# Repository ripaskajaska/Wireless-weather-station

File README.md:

# Wireless-weather-station
Aalto University’s ELEC-8701 Elektronics workshop courses repository for Axel Soderberg, Roope Jaskari and Kalle Aro

# Basic git usage for this project:

Sections 1 to 2 are done on the command line
# 1. Initialization 

If you don't have an ssh key yet follow the instruction in [this link](https://www.howtogeek.com/762863/how-to-generate-ssh-keys-in-windows-10-and-windows-11/)
Add this ssh key to your GitHub SSH keys and proceed.

## clone project
```
git clone git@github.com:<yourusername>/Wireless-weather-station.git
```

Go to the cloned repository > "Wireless-weather-station" (default name)

## Make your own branch
```
git branch <your own branch name here>
```
```
git checkout <your own branch name here>
```
# 2. Working with git

When you want to commit something, first check out the changes you have made.
```
git status
```
After this add the files you'd like to commit

```
git add <your file/folder in the git initialized folder>
```
Commit
```
git commit -m "<your required message here>"
```
And if this is your first push to the git repository use this to also set your upstream:

```
git push --set-upstream origin
```
Otherwise:
```
git push
```

# 3. Merging with main
After a successful commit and push, if you'd like to begin a merge request with your branch and the main branch, navigate to your branch in GitHub from this dropdown:

And then make a pull request here: 

After this, notify the other contributors about the pull request in order to get their approval on the matter. Success!

# In addition one can delete their own branch from the GitHub to start a new addition to the project from a clean table. 
# DO NOT TRY TO DELETE THE MAIN BRANCH!

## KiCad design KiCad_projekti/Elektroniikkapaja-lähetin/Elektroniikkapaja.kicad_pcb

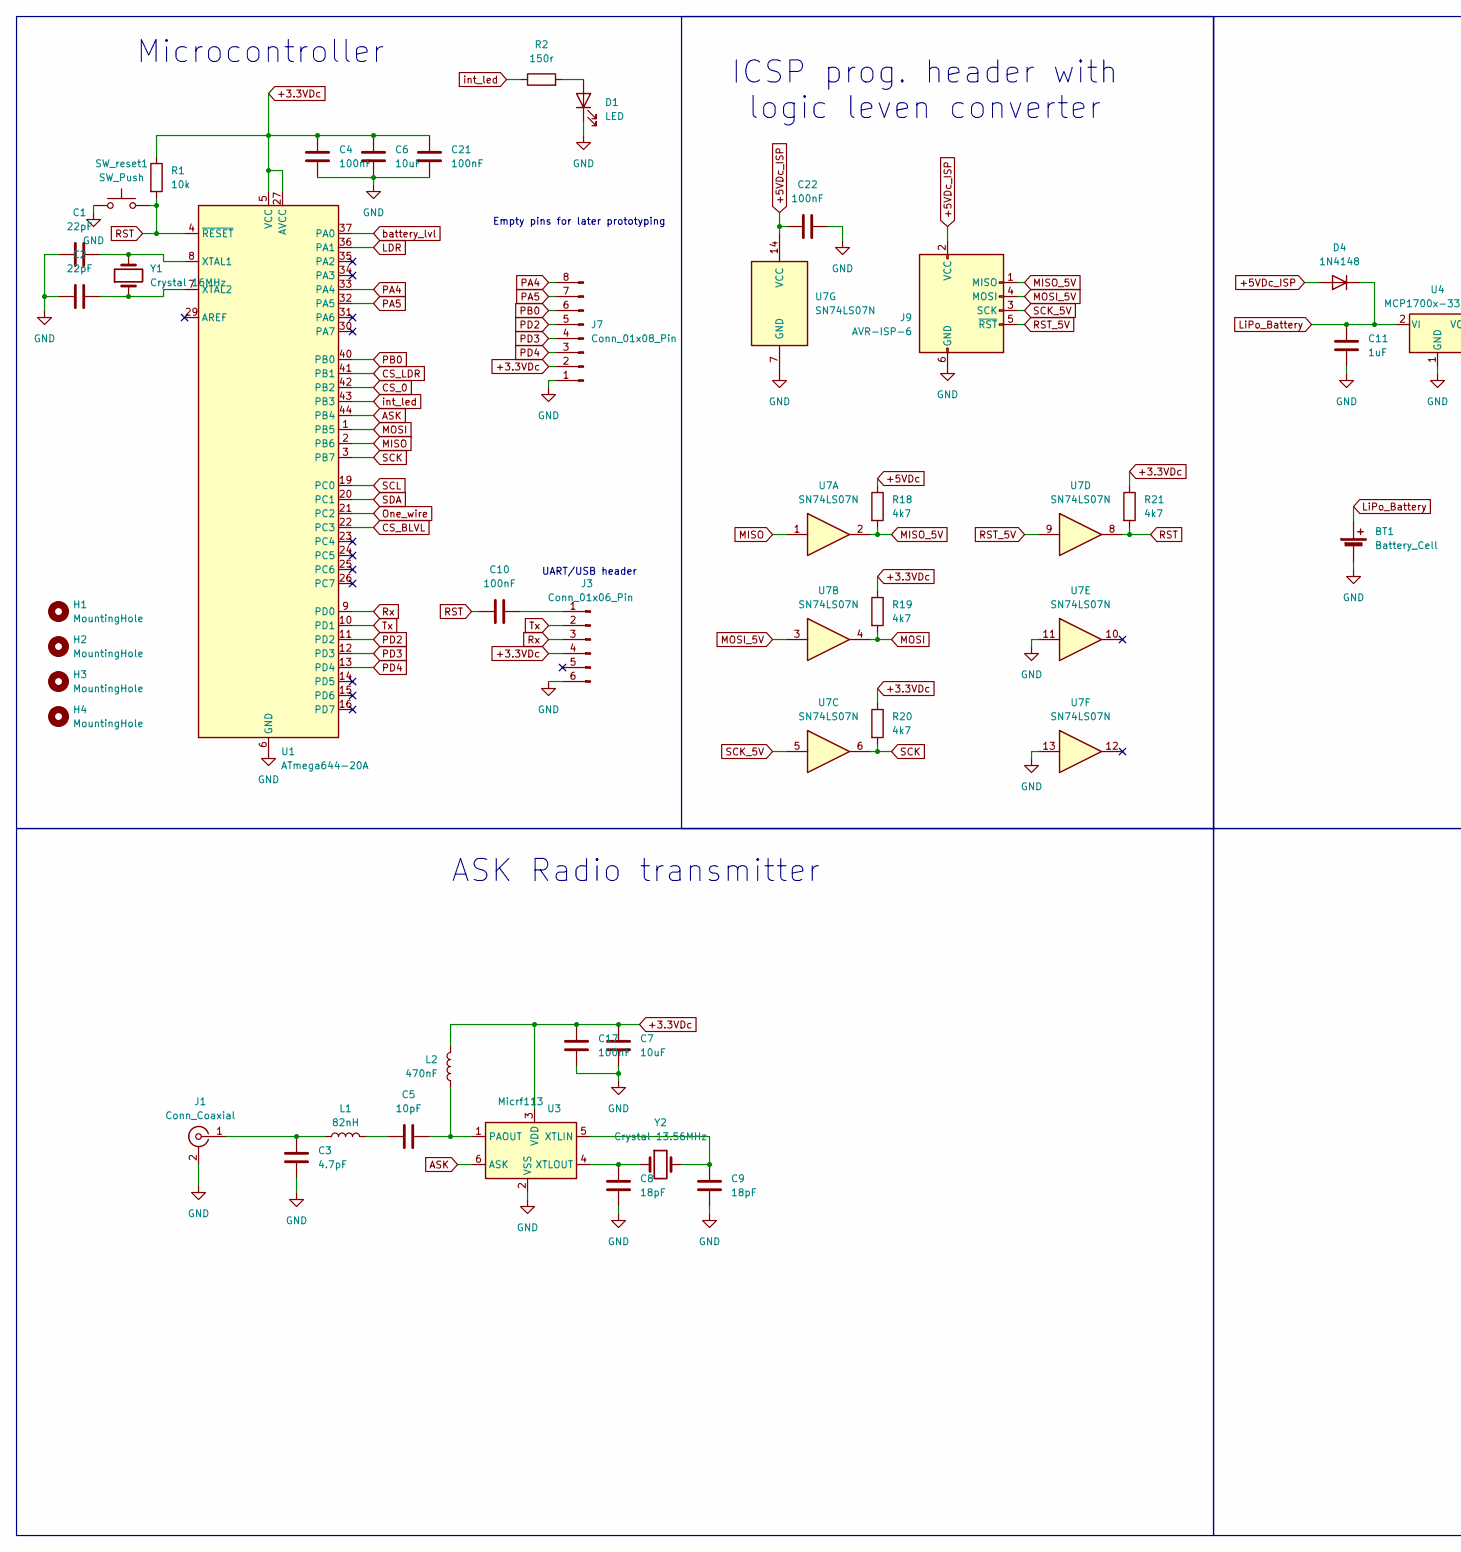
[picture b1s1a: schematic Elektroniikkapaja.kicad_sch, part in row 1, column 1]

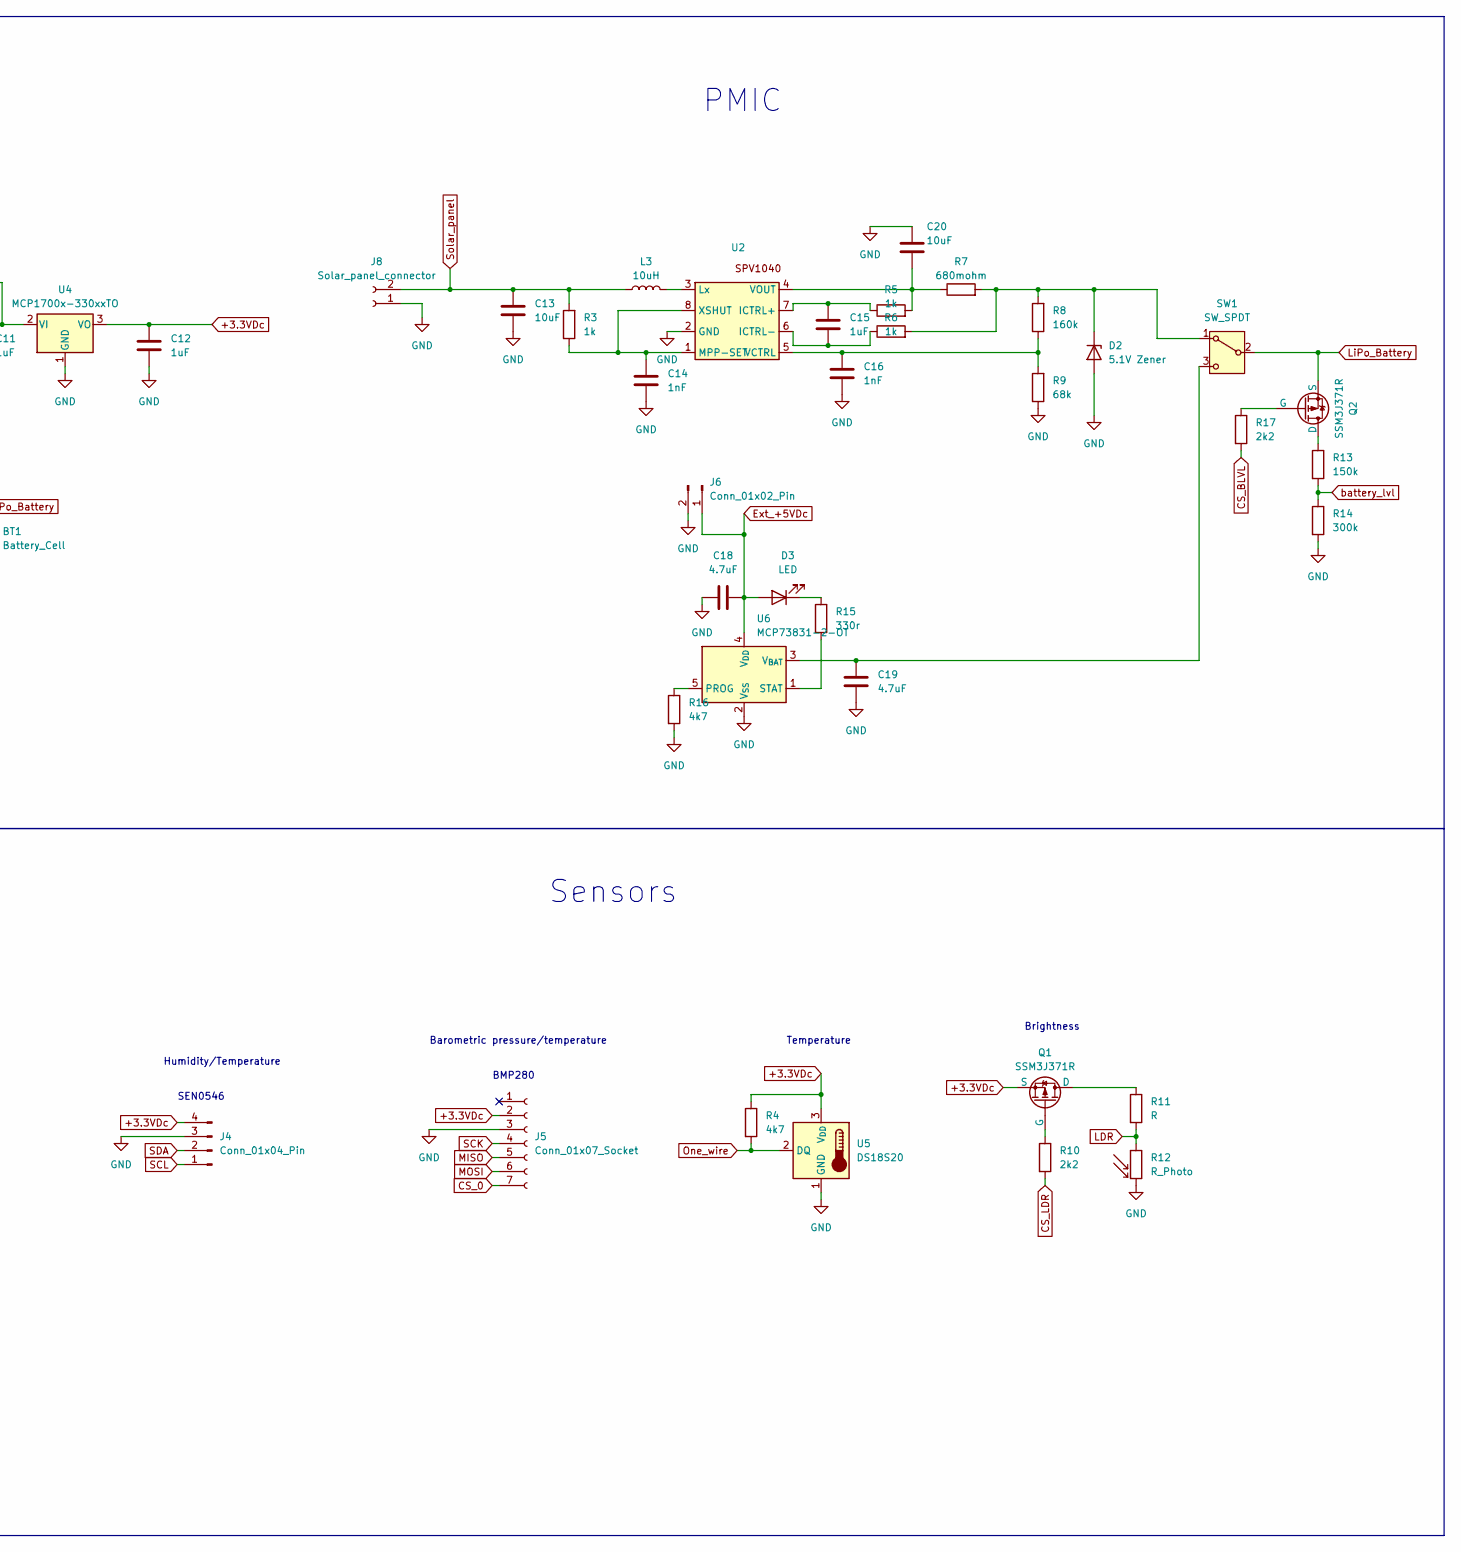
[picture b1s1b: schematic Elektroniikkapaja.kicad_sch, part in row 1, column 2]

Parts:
BT1: Battery_Cell; BatteryHolder_MPD_BH-18650-PC2
C1, C2: 22pF; C_0805_2012Metric_Pad1.18x1.45mm_HandSolder
C3: 4.7pF; C_0805_2012Metric_Pad1.18x1.45mm_HandSolder
C4, C10, C17, C21, C22: 100nF; C_0805_2012Metric_Pad1.18x1.45mm_HandSolder
C5: 10pF; C_0805_2012Metric_Pad1.18x1.45mm_HandSolder
C6, C7, C13, C20: 10uF; C_0805_2012Metric_Pad1.18x1.45mm_HandSolder
C8, C9: 18pF; C_0805_2012Metric_Pad1.18x1.45mm_HandSolder
C11, C12, C15: 1uF; C_0805_2012Metric_Pad1.18x1.45mm_HandSolder
C14, C16: 1nF; C_0805_2012Metric_Pad1.18x1.45mm_HandSolder
C18, C19: 4.7uF; C_1206_3216Metric_Pad1.33x1.80mm_HandSolder
D1, D3: LED; LED_0805_2012Metric_Pad1.15x1.40mm_HandSolder
D2: 5.1V Zener; D_DO-35_SOD27_P7.62mm_Horizontal
D4: 1N4148; D_DO-35_SOD27_P7.62mm_Horizontal
H1, H2, H3, H4: MountingHole; MountingHole_2.2mm_M2
J1: Conn_Coaxial; SMA_Amphenol_901-143_Horizontal
J3: Conn_01x06_Pin; PinHeader_1x06_P2.54mm_Vertical
J4: Conn_01x04_Pin; PinHeader_1x04_P2.54mm_Vertical
J5: Conn_01x07_Socket; PinSocket_1x07_P2.54mm_Vertical
J6: Conn_01x02_Pin; PinHeader_1x02_P2.54mm_Vertical
J7: Conn_01x08_Pin; PinHeader_1x08_P2.54mm_Vertical
J8: Solar_panel_connector; PinHeader_1x02_P2.54mm_Vertical
J9: AVR-ISP-6; PinHeader_2x03_P2.54mm_Vertical
L1: 82nH; L_0805_2012Metric_Pad1.15x1.40mm_HandSolder
L2: 470nF; L_0805_2012Metric_Pad1.15x1.40mm_HandSolder
L3: 10uH; WE-PD2_1054
Q1, Q2: SSM3J371R; SOT-23-3
R1: 10k; R_0805_2012Metric_Pad1.20x1.40mm_HandSolder
R2: 150r; R_0805_2012Metric_Pad1.20x1.40mm_HandSolder
R3, R5, R6: 1k; R_0805_2012Metric_Pad1.20x1.40mm_HandSolder
R4, R16, R18, R19, R20, R21: 4k7; R_0805_2012Metric_Pad1.20x1.40mm_HandSolder
R7: 680mohm; R_0805_2012Metric_Pad1.20x1.40mm_HandSolder
R8: 160k; R_0805_2012Metric_Pad1.20x1.40mm_HandSolder
R9: 68k; R_0805_2012Metric_Pad1.20x1.40mm_HandSolder
R10, R17: 2k2; R_0805_2012Metric_Pad1.20x1.40mm_HandSolder
R11: R; R_0805_2012Metric_Pad1.20x1.40mm_HandSolder
R12: R_Photo; R_Axial_DIN0204_L3.6mm_D1.6mm_P2.54mm_Vertical
R13: 150k; R_0805_2012Metric_Pad1.20x1.40mm_HandSolder
R14: 300k; R_0805_2012Metric_Pad1.20x1.40mm_HandSolder
R15: 330r; R_0805_2012Metric_Pad1.20x1.40mm_HandSolder
SW1: SW_SPDT; SW_CuK_JS202011CQN_DPDT_Straight
SW_reset1: SW_Push; SW_SPST_TL3305A
U1: ATmega644-20A; TQFP-44_10x10mm_P0.8mm
U2: TSSOP-8_4.4x3mm_P0.65mm
U3: Micrf113; SOT-23-6_Handsoldering
U4: MCP1700x-330xxTO; TO-92_Inline
U5: DS18S20; TO-92_Inline
U6: MCP73831-2-OT; SOT-23-5
U7: SN74LS07N; DIP-14_W7.62mm
Y1: Crystal 16MHz; Crystal_HC49-U_Vertical
Y2: Crystal 13.56MHz; Crystal_HC49-U_Vertical

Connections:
+3.3VDc: C4.1, C6.1, C7.1, C12.1, C17.2, C21.1, J3.4, J4.4, J5.2, J7.2, L2.1, Q1.2 (S), R1.1, R4.1, R19.1, R20.1, R21.1, U1.5 (VCC), U1.17 (VCC), U1.27 (AVCC), U1.38 (VCC), U3.3 (VDD), U4.3 (VO), U5.3 (V_{DD})
+5VDc: R18.1
+5VDc_ISP: C22.1, D4.2 (A), J9.2 (VCC), U7.14 (VCC)
ASK: U1.44 (PB4), U3.6 (ASK)
CS_0: J5.7, U1.42 (PB2)
CS_BLVL: R17.2, U1.22 (PC3)
CS_LDR: R10.2, U1.41 (PB1)
Ext_+5VDc: C18.1, D3.2 (A), J6.1, U6.4 (V_{DD})
GND: BT1.2 (-), C1.1, C2.1, C3.2, C4.2, C6.2, C7.2, C8.2, C9.2, C11.2, C12.2, C13.2, C14.2, C16.2, C17.1, C18.2, C19.2, C20.1, C21.2, C22.2, D1.1 (K), D2.2 (A), J1.2 (Ext), J3.6, J4.3, J5.3, J6.2, J7.1, J8.1, J9.6 (GND), R9.1, R12.2, R14.2, R16.2, SW_reset1.1, U1.6 (GND), U1.18 (GND), U1.28 (GND), U1.39 (GND), U2.2 (GND), U3.2 (VSS), U4.1 (GND), U5.1 (GND), U6.2 (V_{SS}), U7.7 (GND), U7.11, U7.13
LDR: R11.2, R12.1, U1.36 (PA1)
LiPo_Battery: BT1.1 (+), C11.1, D4.1 (K), Q2.2 (S), SW1.2 (B), U4.2 (VI)
MISO: J5.5, U1.2 (PB6), U7.1
MISO_5V: J9.1 (MISO), R18.2, U7.2
MOSI: J5.6, R19.2, U1.1 (PB5), U7.4
MOSI_5V: J9.4 (MOSI), U7.3
unnamed: C5.1, L1.2
unnamed: D1.2 (A), R2.2
unnamed: D2.1 (K), R6.2, R7.2, R8.2, SW1.1 (A)
unnamed: D3.1 (K), R15.1
unnamed: C3.1, J1.1 (In), L1.1
unnamed: C10.2, J3.1
unnamed: Q1.3 (D), R11.1
unnamed: Q1.1 (G), R10.1
unnamed: Q2.3 (D), R13.1
unnamed: Q2.1 (G), R17.1
unnamed: C19.1, SW1.3 (C), U6.3 (V_{BAT})
unnamed: C1.2, U1.8 (XTAL1), Y1.2
unnamed: C2.2, U1.7 (XTAL2), Y1.1
unnamed: C15.1, R5.1, U2.7 (ICTRL+)
unnamed: C15.2, R6.1, U2.6 (ICTRL-)
unnamed: L3.2, U2.3 (Lx)
unnamed: C14.1, R3.1, U2.1 (MPP-SET), U2.8 (XSHUT)
unnamed: C16.1, R8.1, R9.2, U2.5 (VCTRL)
unnamed: C20.2, R5.2, R7.1, U2.4 (VOUT)
unnamed: C5.2, L2.2, U3.1 (PAOUT)
unnamed: C9.1, U3.5 (XTLIN), Y2.2
unnamed: C8.1, U3.4 (XTLOUT), Y2.1
unnamed: R16.1, U6.5 (PROG)
unnamed: R15.2, U6.1 (STAT)
One_wire: R4.2, U1.21 (PC2), U5.2 (DQ)
PA4: J7.8, U1.33 (PA4)
PA5: J7.7, U1.32 (PA5)
PB0: J7.6, U1.40 (PB0)
PD2: J7.5, U1.11 (PD2)
PD3: J7.4, U1.12 (PD3)
PD4: J7.3, U1.13 (PD4)
RST: C10.1, R1.2, R21.2, SW_reset1.2, U1.4 (~RESET), U7.8
RST_5V: J9.5 (~RST), U7.9
Rx: J3.3, U1.9 (PD0)
SCK: J5.4, R20.2, U1.3 (PB7), U7.6
SCK_5V: J9.3 (SCK), U7.5
SCL: J4.1, U1.19 (PC0)
SDA: J4.2, U1.20 (PC1)
Solar_panel: C13.1, J8.2, L3.1, R3.2
Tx: J3.2, U1.10 (PD1)
battery_lvl: R13.2, R14.1, U1.37 (PA0)
int_led: R2.1, U1.43 (PB3)

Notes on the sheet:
Temperature
Empty pins for later prototyping
UART/USB header
Microcontroller
Humidity/Temperature
PMIC
Barometric pressure/temperature
BMP280
ICSP prog. header with logic leven converter
ASK Radio transmitter
SEN0546
Brightness
Sensors

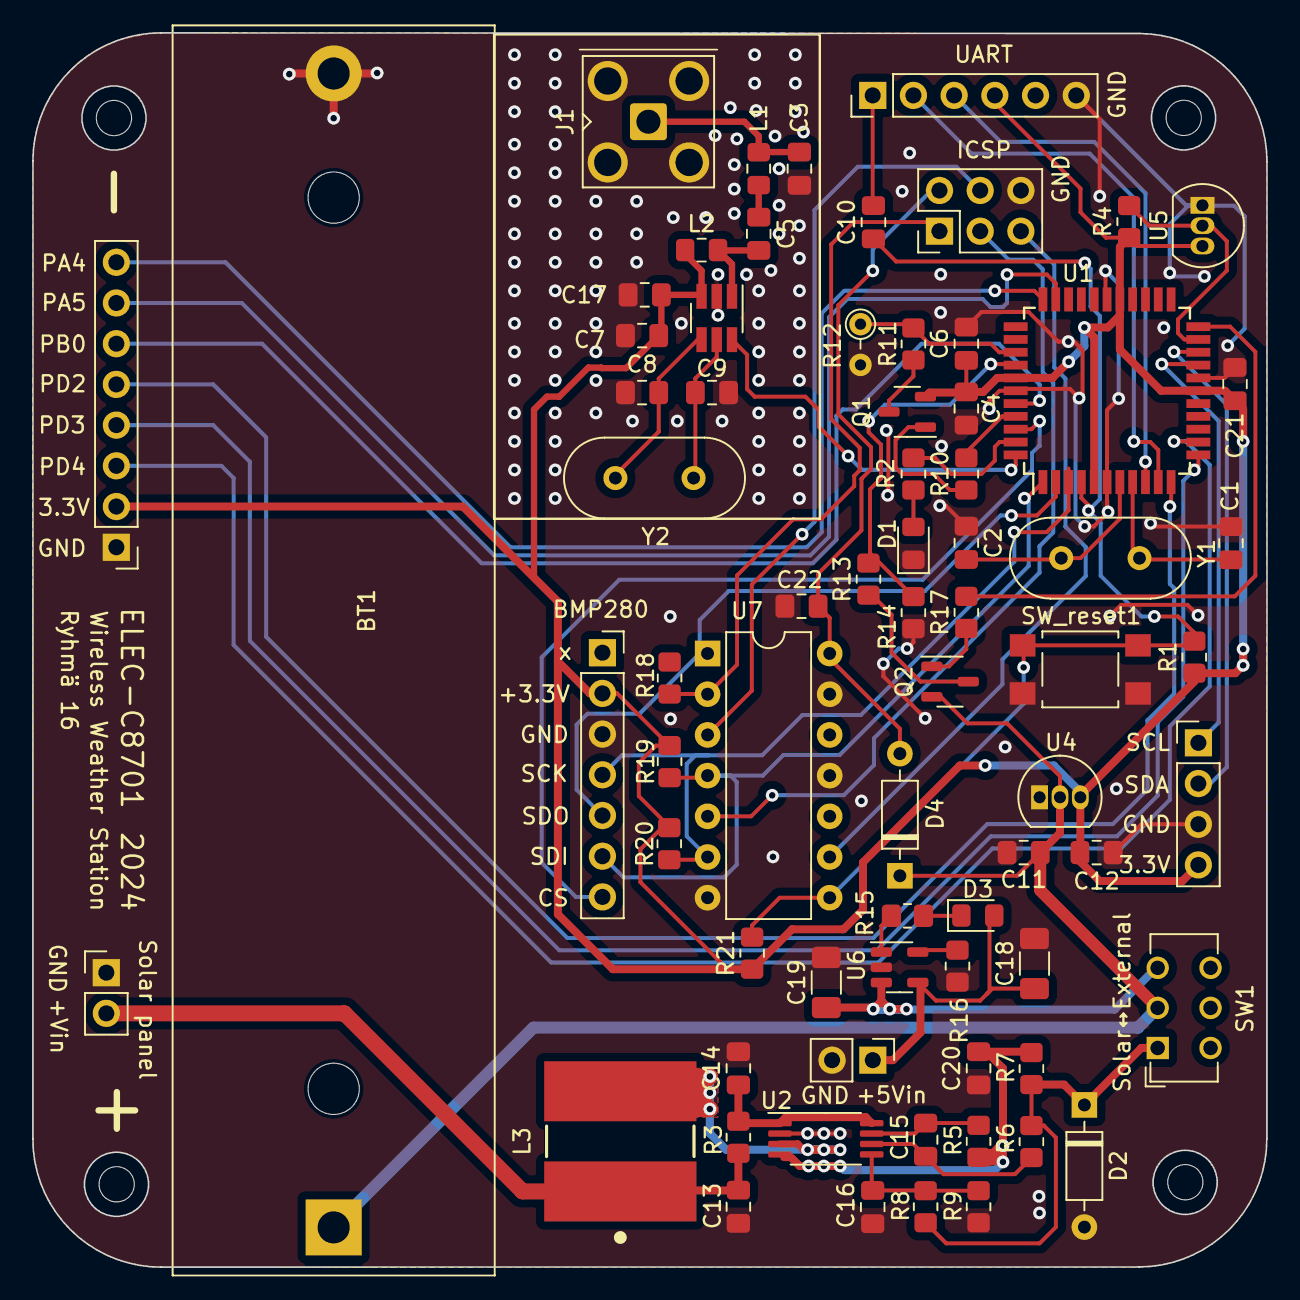
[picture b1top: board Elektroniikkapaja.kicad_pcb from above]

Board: 2 copper layers, 77.0 x 77.0 mm, 76 parts (0 on the bottom side), 56 nets.

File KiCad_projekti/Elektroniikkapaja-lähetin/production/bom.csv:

Designator,Footprint,Quantity,Value,LCSC Part #
BT1,BatteryHolder_MPD_BH-18650-PC2,1,Battery_Cell,
"C1, C2",0805,2,22pF,
"C10, C17, C21, C22, C4",0805,5,100nF,
"C11, C12, C15",0805,3,1uF,
"C13, C20, C6, C7",0805,4,10uF,
"C14, C16",0805,2,1nF,
"C18, C19",1206,2,4.7uF,
C3,0805,1,4.7pF,
C5,0805,1,10pF,
"C8, C9",0805,2,18pF,
"D1, D3",0805,2,LED,
D2,D_DO-35_SOD27_P7.62mm_Horizontal,1,5.1V Zener,
D4,D_DO-35_SOD27_P7.62mm_Horizontal,1,1N4148,
"H1, H2, H3, H4",MountingHole_2.2mm_M2,4,MountingHole,
J1,SMA_Amphenol_901-143_Horizontal,1,Conn_Coaxial,
J3,PinHeader_1x06_P2.54mm_Vertical,1,Conn_01x06_Pin,
J4,PinHeader_1x04_P2.54mm_Vertical,1,Conn_01x04_Pin,
J5,PinSocket_1x07_P2.54mm_Vertical,1,Conn_01x07_Socket,
J6,PinHeader_1x02_P2.54mm_Vertical,1,Conn_01x02_Pin,
J7,PinHeader_1x08_P2.54mm_Vertical,1,Conn_01x08_Pin,
J8,PinHeader_1x02_P2.54mm_Vertical,1,Solar_panel_connector,
J9,PinHeader_2x03_P2.54mm_Vertical,1,AVR-ISP-6,
L1,0805,1,82nH,
L2,0805,1,470nF,
L3,WE-PD2_1054,1,10uH,
"Q1, Q2",SOT-23-3,2,SSM3J371R,
R1,0805,1,10k,
"R10, R17",0805,2,2k2,
R11,0805,1,R,
R12,R_Axial_DIN0204_L3.6mm_D1.6mm_P2.54mm_Vertical,1,R_Photo,
R13,0805,1,150k,
R14,0805,1,300k,
R15,0805,1,330r,
"R16, R18, R19, R20, R21, R4",0805,6,4k7,
R2,0805,1,150r,
"R3, R5, R6",0805,3,1k,
R7,0805,1,680mohm,
R8,0805,1,160k,
R9,0805,1,68k,
SW1,SW_CuK_JS202011CQN_DPDT_Straight,1,SW_SPDT,
SW_RESET1,SW_SPST_TL3305A,1,SW_Push,
U1,TQFP-44_10x10mm_P0.8mm,1,ATmega644-20A,
U2,TSSOP-8_4.4x3mm_P0.65mm,1,~,
U3,SOT-23-6_Handsoldering,1,Micrf113,
U4,TO-92_Inline,1,MCP1700x-330xxTO,
U5,TO-92_Inline,1,DS18S20,
U6,SOT-23-5,1,MCP73831-2-OT,
U7,DIP-14_W7.62mm,1,SN74LS07N,
Y1,Crystal_HC49-U_Vertical,1,Crystal 16MHz,
Y2,Crystal_HC49-U_Vertical,1,Crystal 13.56MHz,

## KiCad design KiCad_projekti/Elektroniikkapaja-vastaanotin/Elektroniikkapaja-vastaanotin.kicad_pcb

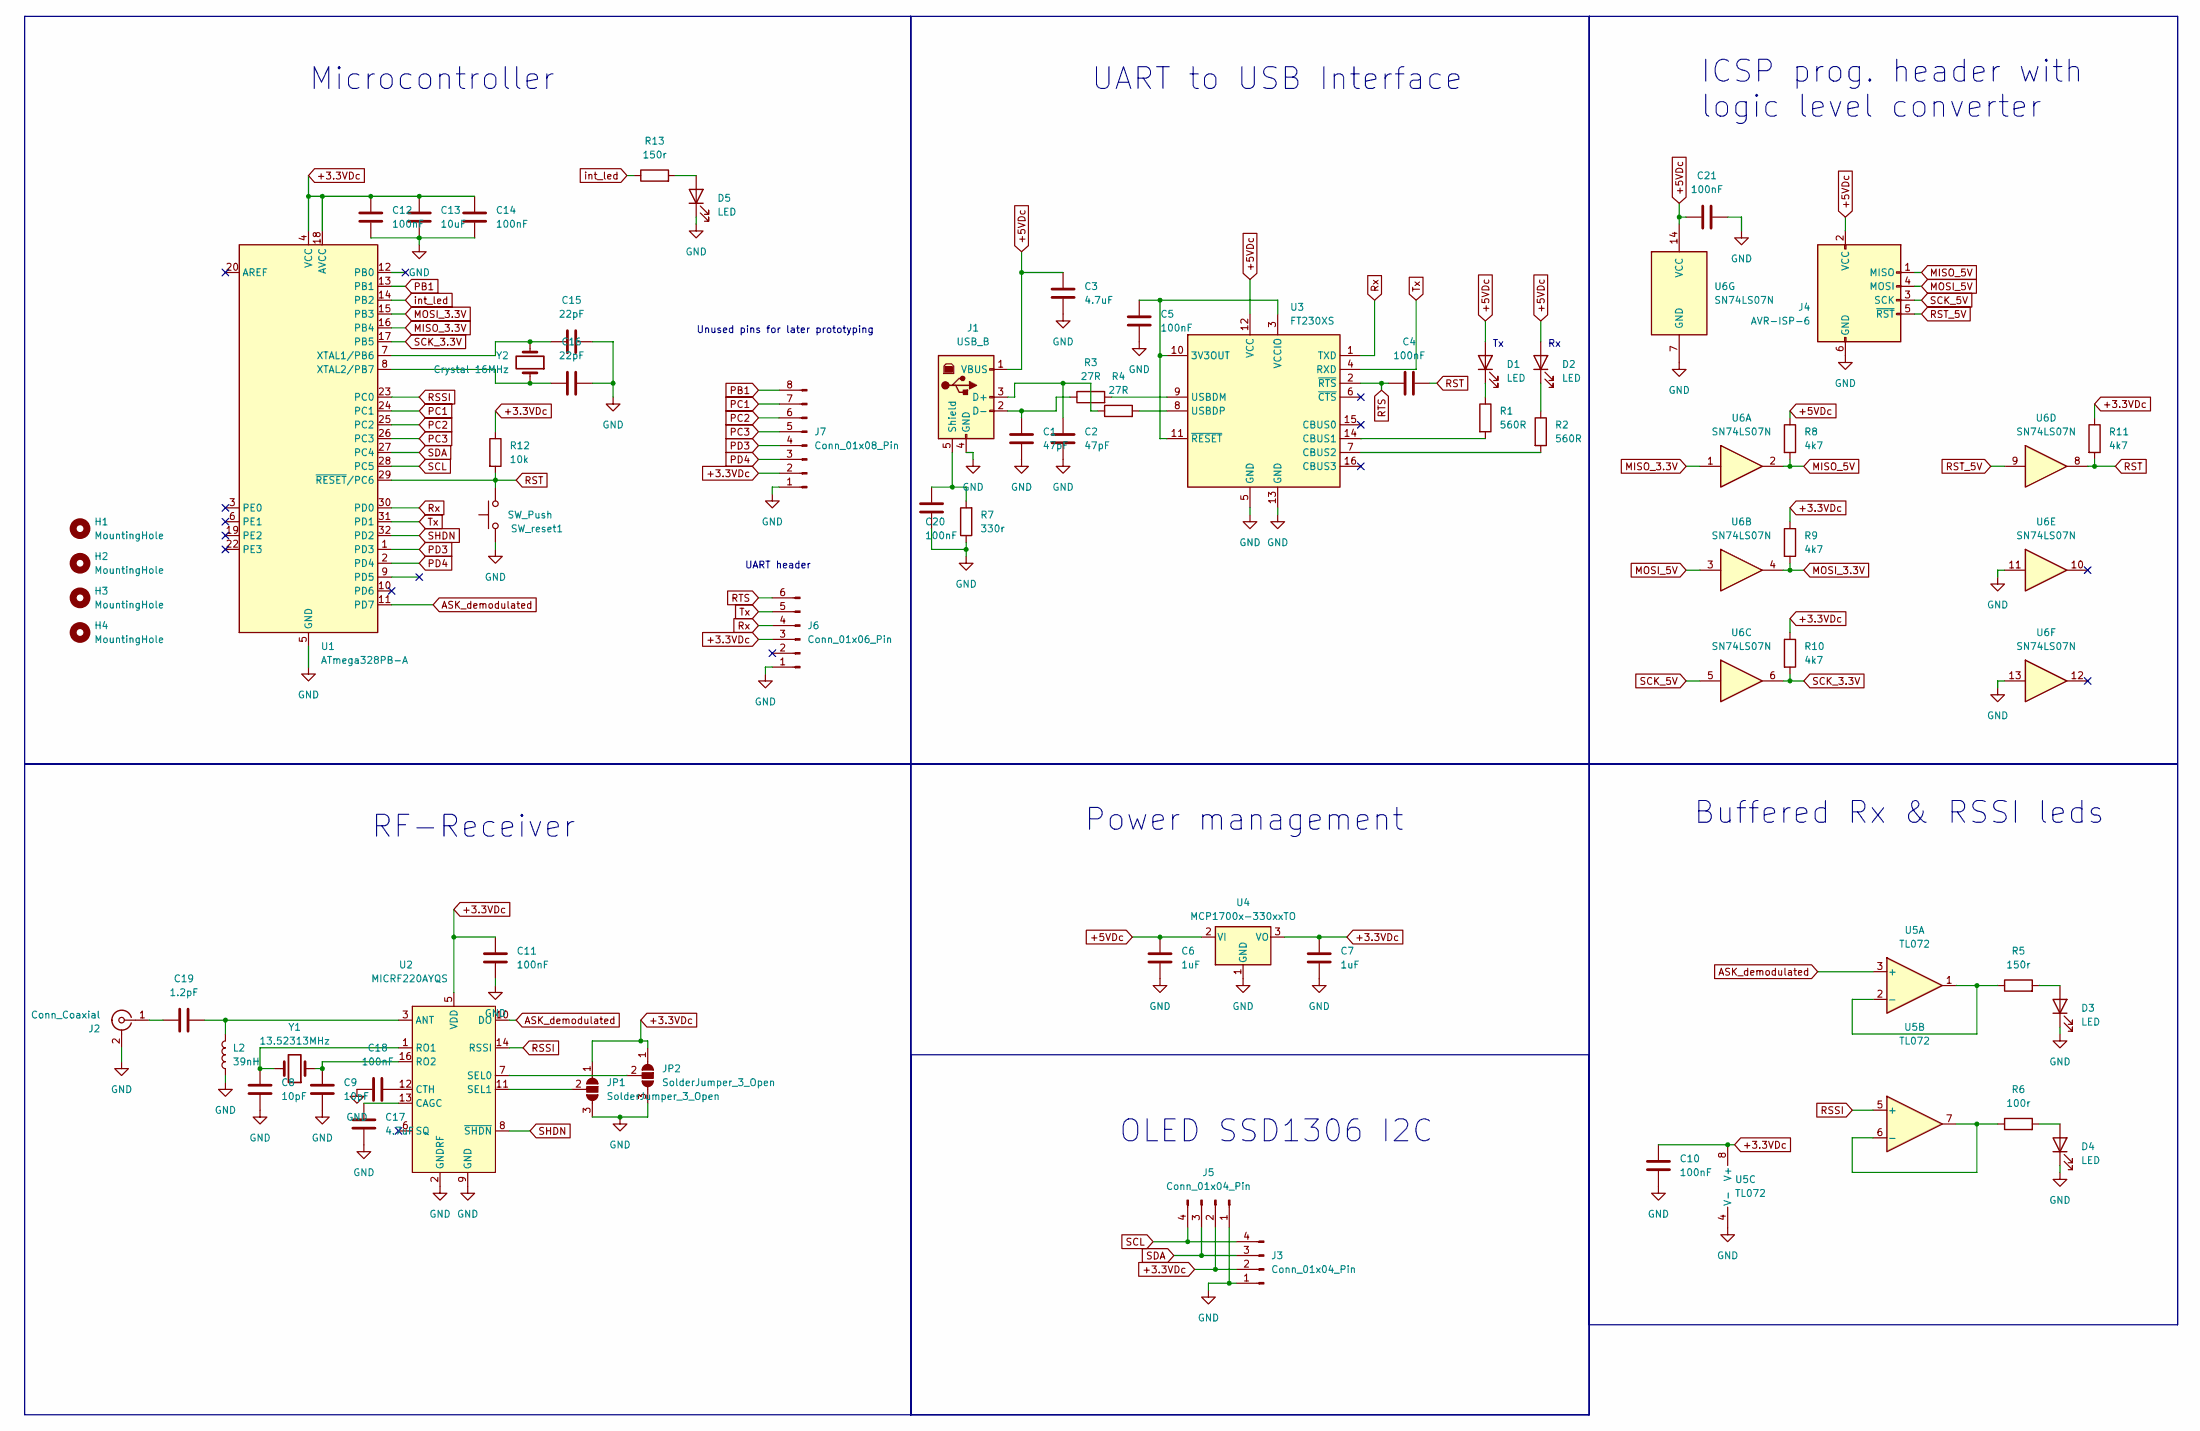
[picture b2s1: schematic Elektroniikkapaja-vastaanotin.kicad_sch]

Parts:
C1, C2: 47pF; C_0805_2012Metric_Pad1.18x1.45mm_HandSolder
C3, C17: 4.7uF; C_1206_3216Metric_Pad1.33x1.80mm_HandSolder
C4, C5, C10, C11, C12, C14, C18, C20, C21: 100nF; C_0805_2012Metric_Pad1.18x1.45mm_HandSolder
C6, C7: 1uF; C_0805_2012Metric_Pad1.18x1.45mm_HandSolder
C8, C9: 10pF; C_0805_2012Metric_Pad1.18x1.45mm_HandSolder
C13: 10uF; C_0805_2012Metric_Pad1.18x1.45mm_HandSolder
C15, C16: 22pF; C_0805_2012Metric_Pad1.18x1.45mm_HandSolder
C19: 1.2pF; C_0805_2012Metric_Pad1.18x1.45mm_HandSolder
D1, D2, D3, D4, D5: LED; LED_0805_2012Metric_Pad1.15x1.40mm_HandSolder
H1, H2, H3, H4: MountingHole; MountingHole_2.2mm_M2
J1: USB_B; USB_B_Lumberg_2411_02_Horizontal
J2: Conn_Coaxial; SMA_Amphenol_901-143_Horizontal
J3: Conn_01x04_Pin; JST_SH_SM04B-SRSS-TB_1x04-1MP_P1.00mm_Horizontal
J4: AVR-ISP-6; PinHeader_2x03_P2.54mm_Vertical
J5: Conn_01x04_Pin; PinHeader_1x04_P2.54mm_Vertical
J6: Conn_01x06_Pin; PinHeader_1x06_P2.54mm_Vertical
J7: Conn_01x08_Pin; PinHeader_1x08_P2.54mm_Vertical
JP1, JP2: SolderJumper_3_Open; SolderJumper-3_P1.3mm_Open_RoundedPad1.0x1.5mm_NumberLabels
L2: 39nH; C_0805_2012Metric_Pad1.18x1.45mm_HandSolder
R1, R2: 560R; R_0805_2012Metric_Pad1.20x1.40mm_HandSolder
R3, R4: 27R; R_0805_2012Metric_Pad1.20x1.40mm_HandSolder
R5: 150r; R_0805_2012Metric_Pad1.20x1.40mm_HandSolder
R6: 100r; R_0805_2012Metric_Pad1.20x1.40mm_HandSolder
R7: 330r; R_0805_2012Metric_Pad1.20x1.40mm_HandSolder
R8, R9, R10, R11: 4k7; R_0805_2012Metric_Pad1.20x1.40mm_HandSolder
R12: 10k; R_0805_2012Metric_Pad1.20x1.40mm_HandSolder
R13: 150r; R_0805_2012Metric
SW_reset1: SW_Push; SW_SPST_TL3305A
U1: ATmega328PB-A; TQFP-32_7x7mm_P0.8mm
U2: MICRF220AYQS; QSOP-16_3.9x4.9mm_P0.635mm
U3: FT230XS; SSOP-16_3.9x4.9mm_P0.635mm
U4: MCP1700x-330xxTO; TO-92_Inline
U5: TL072; SOIC-8_3.9x4.9mm_P1.27mm
U6: SN74LS07N; DIP-14_W7.62mm
Y1: 13.52313MHz; Crystal_SMD_HC49-SD_HandSoldering
Y2: Crystal 16MHz; Crystal_HC49-U_Vertical

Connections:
+3.3VDc: C7.1, C10.1, C11.1, C12.1, C13.1, C14.1, J3.2, J5.2, J6.3, J7.2, JP1.1 (A), JP2.1 (A), R9.1, R10.1, R11.1, R12.1, U1.4 (VCC), U1.18 (AVCC), U2.5 (VDD), U4.3 (VO), U5.8 (V+)
+5VDc: C3.1, C6.1, C21.1, D1.2 (A), D2.2 (A), J1.1 (VBUS), J4.2 (VCC), R8.1, U3.12 (VCC), U4.2 (VI), U6.14 (VCC)
ASK_demodulated: U1.11 (PD7), U2.10 (DO), U5.3 (+)
GND: C1.2, C2.2, C3.2, C5.2, C6.2, C7.2, C8.2, C9.2, C10.2, C11.2, C12.2, C13.2, C14.2, C15.1, C16.1, C17.2, C18.1, C20.2, C21.2, D3.1 (K), D4.1 (K), D5.1 (K), J1.4 (GND), J2.2 (Ext), J3.1, J4.6 (GND), J5.1, J6.1, J7.1, JP1.3 (B), JP2.3 (B), L2.1, R7.1, SW_reset1.1, U1.5 (GND), U1.21 (GND), U2.2 (GNDRF), U2.4 (GNDRF), U2.9 (GND), U3.5 (GND), U3.13 (GND), U4.1 (GND), U5.4 (V-), U6.7 (GND), U6.11, U6.13
MISO_3.3V: U1.16 (PB4), U6.1
MISO_5V: J4.1 (MISO), R8.2, U6.2
MOSI_3.3V: R9.2, U1.15 (PB3), U6.4
MOSI_5V: J4.4 (MOSI), U6.3
unnamed: D1.1 (K), R1.1
unnamed: D2.1 (K), R2.1
unnamed: D3.2 (A), R5.2
unnamed: D4.2 (A), R6.2
unnamed: D5.2 (A), R13.2
unnamed: C2.1, J1.3 (D+), R4.1
unnamed: C1.1, J1.2 (D-), R3.1
unnamed: C20.1, J1.5 (Shield), R7.2
unnamed: C19.2, J2.1 (In)
unnamed: JP1.2 (C), U2.11 (SEL1)
unnamed: JP2.2 (C), U2.7 (SEL0)
unnamed: C15.2, U1.7 (XTAL1/PB6), Y2.2
unnamed: C16.2, U1.8 (XTAL2/PB7), Y2.1
unnamed: C19.1, L2.2, U2.3 (ANT)
unnamed: C17.1, U2.13 (CAGC)
unnamed: C18.2, U2.12 (CTH)
unnamed: C8.1, U2.1 (RO1), Y1.2
unnamed: C9.1, U2.16 (RO2), Y1.1
unnamed: C5.1, U3.3 (VCCIO), U3.10 (3V3OUT), U3.11 (~RESET)
unnamed: R1.2, U3.14 (CBUS1)
unnamed: R2.2, U3.7 (CBUS2)
unnamed: R3.2, U3.9 (USBDM)
unnamed: R4.2, U3.8 (USBDP)
unnamed: R5.1, U5.1, U5.2 (-)
unnamed: R6.1, U5.6 (-), U5.7
PB1: J7.8, U1.13 (PB1)
PC1: J7.7, U1.24 (PC1)
PC2: J7.6, U1.25 (PC2)
PC3: J7.5, U1.26 (PC3)
PD3: J7.4, U1.1 (PD3)
PD4: J7.3, U1.2 (PD4)
RSSI: U1.23 (PC0), U2.14 (RSSI), U5.5 (+)
RST: C4.2, R11.2, R12.2, SW_reset1.2, U1.29 (~RESET/PC6), U6.8
RST_5V: J4.5 (~RST), U6.9
RTS: C4.1, J6.6, U3.2 (~RTS)
Rx: J6.4, U1.30 (PD0), U3.1 (TXD)
SCK_3.3V: R10.2, U1.17 (PB5), U6.6
SCK_5V: J4.3 (SCK), U6.5
SCL: J3.4, J5.4, U1.28 (PC5)
SDA: J3.3, J5.3, U1.27 (PC4)
SHDN: U1.32 (PD2), U2.8 (~SHDN)
Tx: J6.5, U1.31 (PD1), U3.4 (RXD)
int_led: R13.1, U1.14 (PB2)

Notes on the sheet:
OLED SSD1306 I2C
Unused pins for later prototyping
UART header
Buffered Rx & RSSI leds
ICSP prog. header with logic level converter
UART to USB Interface
RF-Receiver
Power management
Microcontroller

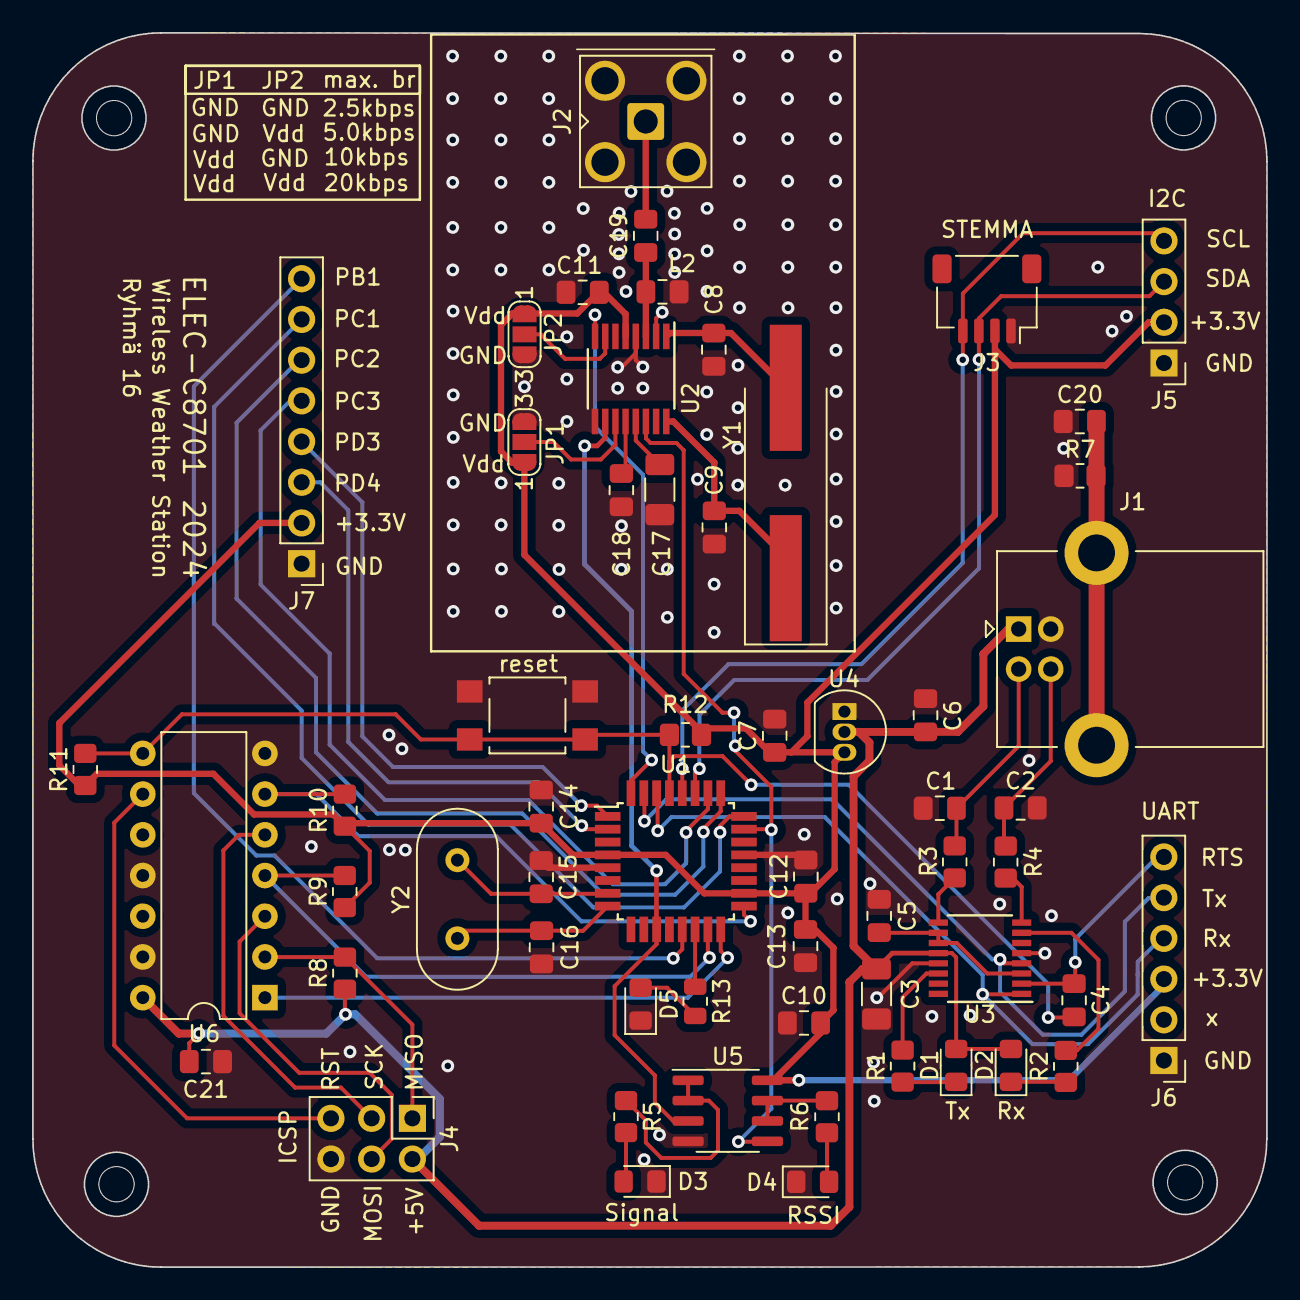
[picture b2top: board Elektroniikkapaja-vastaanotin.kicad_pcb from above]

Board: 2 copper layers, 77.0 x 77.0 mm, 62 parts (0 on the bottom side), 51 nets.

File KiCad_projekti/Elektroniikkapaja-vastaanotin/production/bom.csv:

Designator,Footprint,Quantity,Value,LCSC Part #
"C1, C2",0805,2,47pF,
"C10, C11, C12, C14, C18, C20, C21, C4, C5",0805,9,100nF,
C13,0805,1,10uF,
"C15, C16",0805,2,22pF,
"C17, C3",1206,2,4.7uF,
C19,0805,1,1.2pF,
"C6, C7",0805,2,1uF,
"C8, C9",0805,2,10pF,
"D1, D2, D3, D4, D5",0805,5,LED,
"H1, H2, H3, H4",MountingHole_2.2mm_M2,4,MountingHole,
J1,USB_B_Lumberg_2411_02_Horizontal,1,USB_B,
J2,SMA_Amphenol_901-143_Horizontal,1,Conn_Coaxial,
J3,JST_SH_SM04B-SRSS-TB_1x04-1MP_P1.00mm_Horizontal,1,Conn_01x04_Pin,
J4,PinHeader_2x03_P2.54mm_Vertical,1,AVR-ISP-6,
J5,PinHeader_1x04_P2.54mm_Vertical,1,Conn_01x04_Pin,
J6,PinHeader_1x06_P2.54mm_Vertical,1,Conn_01x06_Pin,
J7,PinHeader_1x08_P2.54mm_Vertical,1,Conn_01x08_Pin,
"JP1, JP2",SolderJumper-3_P1.3mm_Open_RoundedPad1.0x1.5mm_NumberLabels,2,SolderJumper_3_Open,
L2,0805,1,39nH,
"R1, R2",0805,2,560R,
"R10, R11, R8, R9",0805,4,4k7,
R12,0805,1,10k,
"R13, R5",0805,2,150r,
"R3, R4",0805,2,27R,
R6,0805,1,100r,
R7,0805,1,330r,
SW_RESET1,SW_SPST_TL3305A,1,SW_Push,
U1,TQFP-32_7x7mm_P0.8mm,1,ATmega328PB-A,
U2,QSOP-16_3.9x4.9mm_P0.635mm,1,MICRF220AYQS,
U3,SSOP-16_3.9x4.9mm_P0.635mm,1,FT230XS,
U4,TO-92_Inline,1,MCP1700x-330xxTO,
U5,SOIC-8_3.9x4.9mm_P1.27mm,1,TL072,
U6,DIP-14_W7.62mm,1,SN74LS07N,
Y1,Crystal_SMD_HC49-SD_HandSoldering,1,13.52313MHz,
Y2,Crystal_HC49-U_Vertical,1,Crystal 16MHz,

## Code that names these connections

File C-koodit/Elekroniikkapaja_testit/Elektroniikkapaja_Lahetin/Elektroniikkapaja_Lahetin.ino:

//Include libraries
#include <OneWire.h>
#include <DallasTemperature.h>
#include <RH_ASK.h>
#include <SPI.h> 
#include <Adafruit_BMP280.h>
#include <Wire.h>

//pin definition
#define ONE_WIRE_BUS (PC2)
#define BMP_SCK  (PB7)
#define BMP_MISO (PB6)
#define BMP_MOSI (PB7)
#define BMP_CS   (PB2)
#define address 0x40 //SEN0546 I2C address

//global variables
float temp = 0.0;
float pressure = 0.0;
float humidity = 0.0; 
float battery_voltage = 0.0;
uint8_t buf[4] = {0};
uint16_t rawHumidity;

//function prototypes
void transmit_data_packet()
void measure_barometric_pressure(float* pressure_ptr);
void measure_relative_humidity(float* humidity_ptr);
void measure_temperature(float* temp_ptr);
void measure_battery_voltage(float* battery_voltage);
uint8_t readReg(uint8_t reg, void* pBuf, size_t size);
//void measure_brightness();


//Initialize dallas temp ds1820
OneWire oneWire(ONE_WIRE_BUS);        // Setup a oneWire instance to communicate with any OneWire devices (not just Maxim/Dallas temperature ICs)
DallasTemperature sensors(&oneWire);  // Pass our oneWire reference to Dallas Temperature. 

//initialize BMP280
Adafruit_BMP280 bmp(BMP_CS); // hardware SPI

void setup() {
  // put your setup code here, to run once:
  pinMode(A0, INPUT);   //battery level
  pinMode(A1, INPUT);   //LDR
  pinMode(PB1, OUTPUT); //CS LDR
  pinMode(PB2, OUTPUT); //CS BMP280
  pinMode(PB3, OUTPUT); //Int led
  pinMode(PB4, OUTPUT); //transmit ASK data pin
  pinMode(PC3, OUTPUT); //CS battery level

  digitalWrite(PC3, HIGH);

   //settings    KATSO TARVITSEEKO TÄTÄ!!!!!
  bmp.setSampling(Adafruit_BMP280::MODE_FORCED,     /* Operating Mode. */
                  Adafruit_BMP280::SAMPLING_X2,     /* Temp. oversampling */
                  Adafruit_BMP280::SAMPLING_X16,    /* Pressure oversampling */
                  Adafruit_BMP280::FILTER_X16,      /* Filtering. */
                  Adafruit_BMP280::STANDBY_MS_500); /* Standby time. */

  //initialize sensors
  sensors.begin();
  bmp.begin();
}

void loop() {

  //measure temperature
  measure_temperature(&temp);

  //measrue barometric pressure
  measure_barometric_pressure(&pressure);

  //measure relative humidity
  measure_relative_humidity(&humidity);
}

void measure_temperature(float* temp_ptr){
   sensors.requestTemperatures(); // Send the command to get temperatures
  * temp_ptr = sensors.getTempCByIndex(0);
}

void measure_barometric_pressure(float* pressure_ptr){
  bmp.takeForcedMeasurement(); // Send the command to get barometric pressure data
  * pressure_ptr = bmp.readPressure();
}

uint8_t readReg(uint8_t reg, void* pBuf, size_t size) {
  if (pBuf == NULL) {
    Serial.println("pBuf ERROR!! : null pointer");
    return 0;
  }
  uint8_t* _pBuf = (uint8_t*)pBuf;
  Wire.beginTransmission(address);
  Wire.write(&reg, 1);
  if (Wire.endTransmission() != 0) {
    return 0;
  }
  delay(20); // Small delay for sensor response
  Wire.requestFrom(address, (uint8_t)size);
  for (uint16_t i = 0; i < size; i++) {
    _pBuf[i] = Wire.read();
  }
  return size;
}

void measure_relative_humidity(float* humidity_ptr){
   if (hum == NULL) {
    Serial.println("Error: null pointer passed to measureHumidity");
    return;
  }

  uint8_t buf[4] = {0};
  uint16_t rawHumidity;

  // Read humidity register (0x00 is assumed as register for simplicity)
  if (readReg(0x00, buf, 4)) {
    rawHumidity = buf[2] << 8 | buf[3];
    *hum = ((float)rawHumidity / 65535.0) * 100; // Update the value at the pointer
  } 
}

void measure_battery_voltage(float* battery_voltage){
  digitalWrite(PC3, LOW); //cs enable for reading votlage
  * battery_voltage = analogRead(A0);
  digitalWrite(PC3, HIGH);
}

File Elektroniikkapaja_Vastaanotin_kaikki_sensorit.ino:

#include <RH_ASK.h>
#include <SPI.h> // Not used but needed for compatibility

/*
PINS:
internal led PB2
RSSI input PC0
ask input PD7
Shutdown PD2
*/

// Create an instance of the RadioHead driver

RH_ASK driver(2000, 7, 9, 15); // (bitrate, RX pin, TX pin, PTT pin)

union FloatToBytes {
    float floatValue;
    byte byteArray[sizeof(float)];
};

void receiveFloats() {
    float buf[4];
    uint8_t buflen = sizeof(buf);
    
    // Receive the packet containing the float (4 bytes)
    if (driver.recv((uint8_t*)buf, &buflen)) {
        
        // get values of buffer and serial print them out
        Serial.print("Temperature: ");
        Serial.print(buf[0], 2);
        Serial.println("°C");

        Serial.print("Pressure: ");
        Serial.print(buf[1], 2);
        Serial.println(" hPa");

        Serial.print("Humidity: ");
        Serial.print(buf[2], 2);
        Serial.println("%");

        Serial.print("Battery voltage: ");
        Serial.print(buf[3], 2);
        Serial.println(" V");
    }
}

void setup() {
    // Initialize the RadioHead driver
    driver.init();
    Serial.begin(9600);
    pinMode(2, OUTPUT);
    pinMode(4, OUTPUT); //reset for atmega328 driving oled
    digitalWrite(2, LOW);
    digitalWrite(4, LOW);
    delay(1000);
    digitalWrite(4, HIGH);

}

void loop() {
    digitalWrite(2, LOW);
    receiveFloats();
    delay(1000); // Wait for a second before receiving again
}

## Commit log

2024-09-09 template for c code
2024-09-12 Added picture
2024-10-05 reads csv file and plots it in time and frequency domain
2024-10-14 Kicadi projekti
2024-10-20 testaus onko oikea versio
2024-10-20 tää pitäs olla oikea versio
2024-10-20 Update README.md
    Updated readme with github instructions
2024-10-21 updates to schematic
2024-10-23 Lähetin ja vastaanotin kicad
2024-11-11 nyt on valmista levyä
2024-12-01 usb com serial reader for final iteration
2024-12-01 Temperature reading application
2024-12-07 koodeja
2024-12-08 Vähä koodailuu vähä
2024-12-09 Vähä korjailua ainakin lähettimen puolella
2024-12-09 Vähä korjailua ainakin lähettimen puolella lisää
2024-12-09 Vähä korjailua ainakin lähettimen puolella lisää taas
2024-12-22 Loppu scripti kai
2024-12-22 Create Raspille_filu
2024-12-29 Siivoilua ja webi-tiedostot kuntoon
2024-12-29 Poistin raspitiedoston, kun se oli vanha
